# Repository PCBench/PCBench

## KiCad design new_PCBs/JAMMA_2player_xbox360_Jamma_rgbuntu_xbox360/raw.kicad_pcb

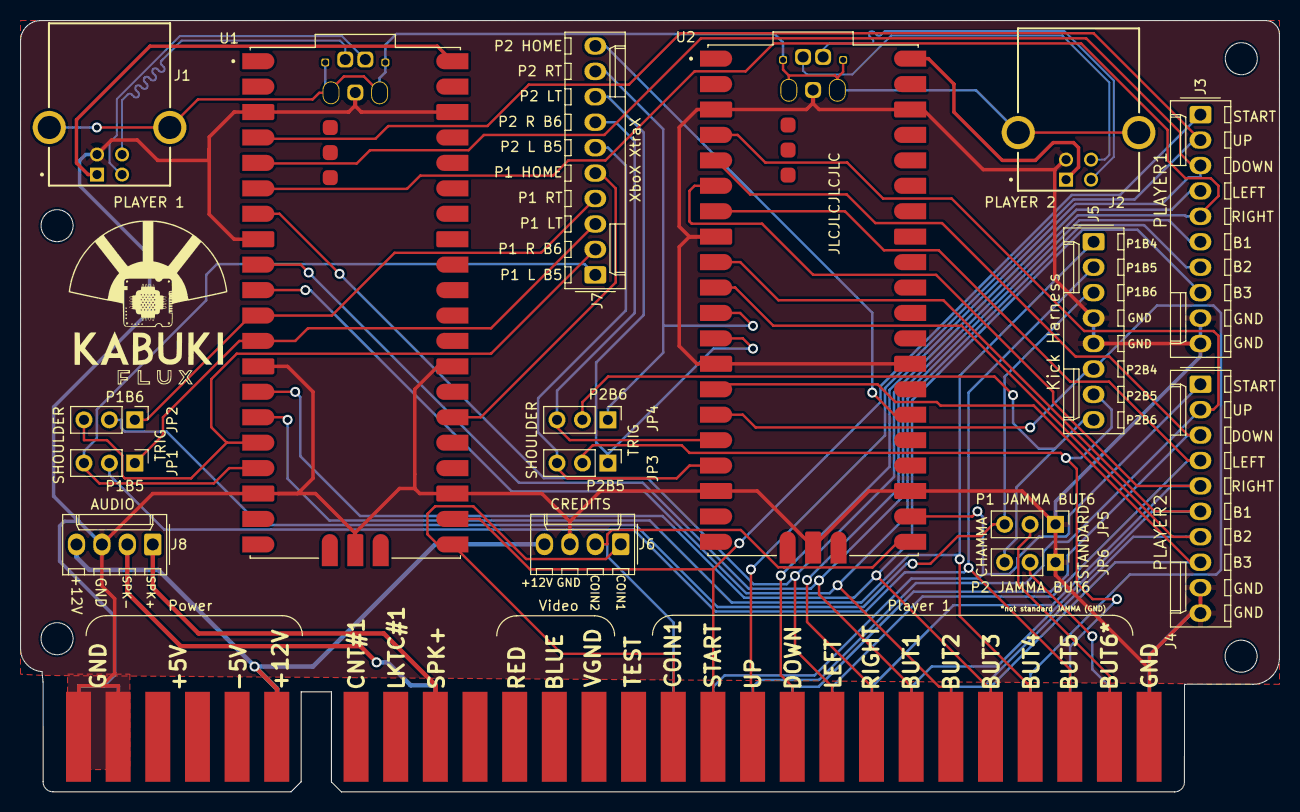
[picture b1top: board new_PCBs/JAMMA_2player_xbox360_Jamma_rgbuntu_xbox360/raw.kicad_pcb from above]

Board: 2 copper layers, 125.7 x 77.0 mm, 22 parts (0 on the bottom side), 47 nets.

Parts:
G1: LOGO; LogoKabuki_18mm
HOLE1, HOLE2, HOLE3, HOLE4: MountingHole_3.2mm_M3
J1: USB-B PICO1; USB-B
J2: USB-B PICO2; USB-B
J3: PLAYER1; Molex_KK-254_AE-6410-10A_1x10_P2.54mm_Vertical
J4: PLAYER2; Molex_KK-254_AE-6410-10A_1x10_P2.54mm_Vertical
J5: Kick Harness; Molex_KK-254_AE-6410-08A_1x08_P2.54mm_Vertical
J6: CREDITS; Molex_KK-254_AE-6410-04A_1x04_P2.54mm_Vertical
J7: XboX XtraX; Molex_KK-254_AE-6410-10A_1x10_P2.54mm_Vertical
J8: AUDIO; Molex_KK-254_AE-6410-04A_1x04_P2.54mm_Vertical
J9: JAMMA_edge_conn; JAMMA_edge
JP1: P1_B5_SELECTOR; PinHeader_1x03_P2.54mm_Vertical
JP2: P1_B6_SELECTOR; PinHeader_1x03_P2.54mm_Vertical
JP3: P2_B5_SELECTOR; PinHeader_1x03_P2.54mm_Vertical
JP4: P2_B6_SELECTOR; PinHeader_1x03_P2.54mm_Vertical
JP5: P1 JAMMA BUT6; PinHeader_1x03_P2.54mm_Vertical
JP6: P2 JAMMA BUT6; PinHeader_1x03_P2.54mm_Vertical
U1, U2: pi_pico; pi-pico

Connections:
/+12V: J6.4, J8.4, J9.6 (+12V), J9.F (+12V)
/GND: J1.4 (GND), J2.4 (GND), J3.9, J3.10, J4.9, J4.10, J5.4, J5.5, J6.3, J8.3, J9.1 (GND), J9.2 (GND), J9.28 (GND), J9.A (GND), J9.B (GND), J9.f (GND), JP5.1 (A), JP6.1 (A), U1.3 (GND), U1.8 (GND), U1.13 (GND), U1.18 (GND), U1.23 (GND), U1.28 (GND), U1.38 (GND), U1.D2 (GND), U1.TP1 (TP1_GND), U2.3 (GND), U2.8 (GND), U2.13 (GND), U2.18 (GND), U2.23 (GND), U2.28 (GND), U2.38 (GND), U2.D2 (GND), U2.TP1 (TP1_GND)
/P1_A_B1: J3.6, J9.22 (Player_1_Button_1), U1.9 (GP6)
/P1_B5: J5.2, J9.26 (Unused), JP1.2 (C)
/P1_B6: J5.3, JP2.2 (C), JP5.3 (B)
/P1_B_B2: J3.7, J9.23 (Player_1_Button_2), U1.10 (GP7)
/P1_COIN_B7: J6.1, J9.16 (Coin_1), U1.21 (GP16)
/P1_DPAD_DOWN: J3.3, J9.19 (Player_1_Down), U1.5 (GP3)
/P1_DPAD_LEFT: J3.4, J9.20 (Player_1_Left), U1.7 (GP5)
/P1_DPAD_RIGHT: J3.5, J9.21 (Player_1_Right), U1.6 (GP4)
/P1_DPAD_UP: J3.2, J9.18 (Player_1_Up), U1.4 (GP2)
/P1_HOME: J7.5, U1.26 (GP20)
/P1_JAMMA_B6_GND: J9.27 (GND), JP5.2 (C)
/P1_LT: J7.3, JP1.1 (A), U1.12 (GP9)
/P1_L_B5: J7.1, JP1.3 (B), U1.17 (GP13)
/P1_RT: J7.4, JP2.1 (A), U1.11 (GP8)
/P1_R_B6: J7.2, JP2.3 (B), U1.16 (GP12)
/P1_START_B8: J3.1, J9.17 (Player_1_Start), U1.22 (GP17)
/P1_X_B3: J3.8, J9.24 (Player_1_Button_3), U1.14 (GP10)
/P1_Y_B4: J5.1, J9.25 (Player_1_Button_4), U1.15 (GP11)
/P2_A_B1: J4.6, J9.Z (Player_2_Button_1), U2.9 (GP6)
/P2_B5: J5.7, J9.d (Unused), JP3.2 (C)
/P2_B6: J5.8, JP4.2 (C), JP6.3 (B)
/P2_B_B2: J4.7, J9.a (Player_2_Button_2), U2.10 (GP7)
/P2_COIN_B7: J6.2, J9.T (Coin_2), U2.21 (GP16)
/P2_DPAD_DOWN: J4.3, J9.W (Player_2_Down), U2.5 (GP3)
/P2_DPAD_LEFT: J4.4, J9.X (Player_2_Left), U2.7 (GP5)
/P2_DPAD_RIGHT: J4.5, J9.Y (Player_2_Right), U2.6 (GP4)
/P2_DPAD_UP: J4.2, J9.V (Player_2_Up), U2.4 (GP2)
/P2_HOME: J7.10, U2.26 (GP20)
/P2_JAMMA_B6_GND: J9.e (GND), JP6.2 (C)
/P2_LT: J7.8, JP3.1 (A), U2.12 (GP9)
/P2_L_B5: J7.6, JP3.3 (B), U2.17 (GP13)
/P2_RT: J7.9, JP4.1 (A), U2.11 (GP8)
/P2_R_B6: J7.7, JP4.3 (B), U2.16 (GP12)
/P2_START_B8: J4.1, J9.U (Player_2_Start), U2.22 (GP17)
/P2_X_B3: J4.8, J9.b (Player_2_Button_3), U2.14 (GP10)
/P2_Y_B4: J5.6, J9.c (Player_2_Button_4), U2.15 (GP11)
/PICO1_D+: J1.3 (D+), U1.TP3 (TP3_USB_DP)
/PICO1_D-: J1.2 (D-), U1.TP2 (TP2_USB_DM)
/PICO2_D+: J2.3 (D+), U2.TP3 (TP3_USB_DP)
/PICO2_D-: J2.2 (D-), U2.TP2 (TP2_USB_DM)
/SPK+: J8.1, J9.10 (Speaker+)
/SPK-: J8.2, J9.L (Speaker-)
/USB_PICO1_VCC: J1.1 (VCC), U1.40 (VBUS)
/USB_PICO2_VCC: J2.1 (VCC), U2.40 (VBUS)
/USB_SHIELD: J1.S1 (SHIELD), J1.S2 (SHIELD), J2.S1 (SHIELD), J2.S2 (SHIELD), U1.A (USB_SHIELD), U1.B (USB_SHIELD), U1.C (USB_SHIELD), U1.D (USB_SHIELD), U2.A (USB_SHIELD), U2.B (USB_SHIELD), U2.C (USB_SHIELD), U2.D (USB_SHIELD)

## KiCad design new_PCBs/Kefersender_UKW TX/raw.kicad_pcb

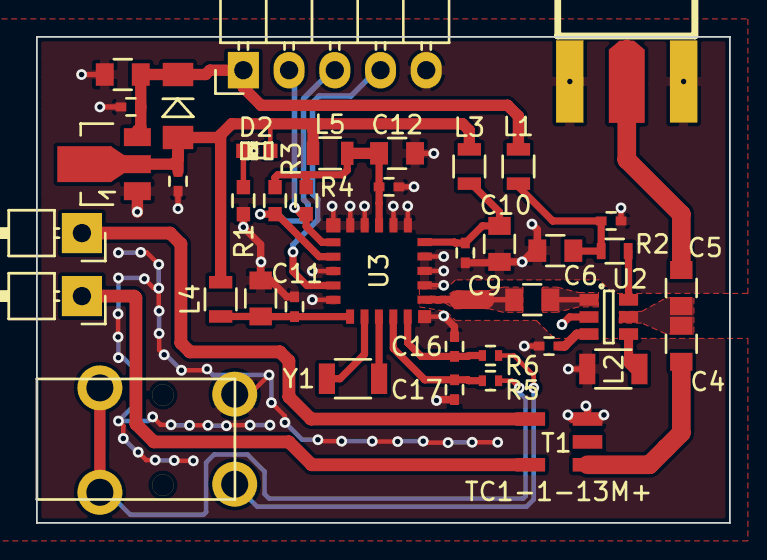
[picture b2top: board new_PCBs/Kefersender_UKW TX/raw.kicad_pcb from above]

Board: 2 copper layers, 38.5 x 27.0 mm, 40 parts (0 on the bottom side), 27 nets.

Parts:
C1, C3, C7, C8, C13, C14, C15: 100n; C_0402
C2, C6, C10, C11, C12: 22µ; C_0805
C4, C5, C9: 1nF; C_0805
C16, C17: 100p; C_0402
CON1: LUM1503
D1: 1n4148; Diode-MiniMELF_Standard
D2: grün; LED-0603
L1, L3, L4, L5: 10µH; R_0805
L2: 470nH; R_1206
P1, P2: CONN_01X01; Pin_Header_Angled_1x01
P3: CONN_01X05; Pin_Header_Angled_1x05
R1: 100; C_0603
R2: 220; R_0603
R3, R4: 4,7k; C_0603
R5, R6: 1k; R_0402
SMA_E1: Platinenkantenbuchse; SMA_EDGE
T1: TC1-1-13M+; AT224-1A
U1: AP1117D33; SOT89-3_Housing
U2: THS9001; SOT-23-6
U3: Alps_603A
Y1: 32,768kHz; R_1206

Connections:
+3V3: C3.1, D1.2, D2.2, L3.1, L4.1, L5.1, U1.2
+5V: C1.1, C2.1, D1.1, L1.2, P3.1, U1.3
/RDS: P3.4, U3.16
/SCL: P3.3, R3.2, U3.14
/SDA: P3.2, R4.2, U3.13
/Ton_L: CON1.2, R5.2
/Ton_R: CON1.3, R6.1
GND: C1.2, C2.2, C3.2, C6.2, C7.2, C8.2, C10.2, C11.2, C12.2, C13.2, C14.2, C15.2, C16.2, C17.2, CON1.1, L2.1, P3.5, R1.2, SMA_E1.0, SMA_E1.2, T1.1, U1.1, U2.2, U3.1, U3.3, U3.4, U3.5, U3.7, U3.8, U3.10, U3.11, U3.12, U3.15, U3.17
unnamed: C4.1, T1.4
unnamed: C4.2, C5.2, U2.5
unnamed: C5.1, SMA_E1.1
unnamed: C6.1, C7.1, L1.1, R2.1
unnamed: C8.1, U2.3
unnamed: C9.1, U2.1
unnamed: C9.2, U3.2
unnamed: C10.1, C13.1, L3.2, U3.6
unnamed: C11.1, C14.1, L4.2, U3.18
unnamed: C12.1, C15.1, L5.2, R3.1, R4.1, U3.9
unnamed: C16.1, R6.2, U3.22
unnamed: C17.1, R5.1, U3.21
unnamed: D2.1, R1.1
unnamed: L2.2, U2.4
unnamed: P1.1, T1.2
unnamed: P2.1, T1.3
unnamed: R2.2, U2.6
unnamed: U3.19, Y1.1
unnamed: U3.20, Y1.2

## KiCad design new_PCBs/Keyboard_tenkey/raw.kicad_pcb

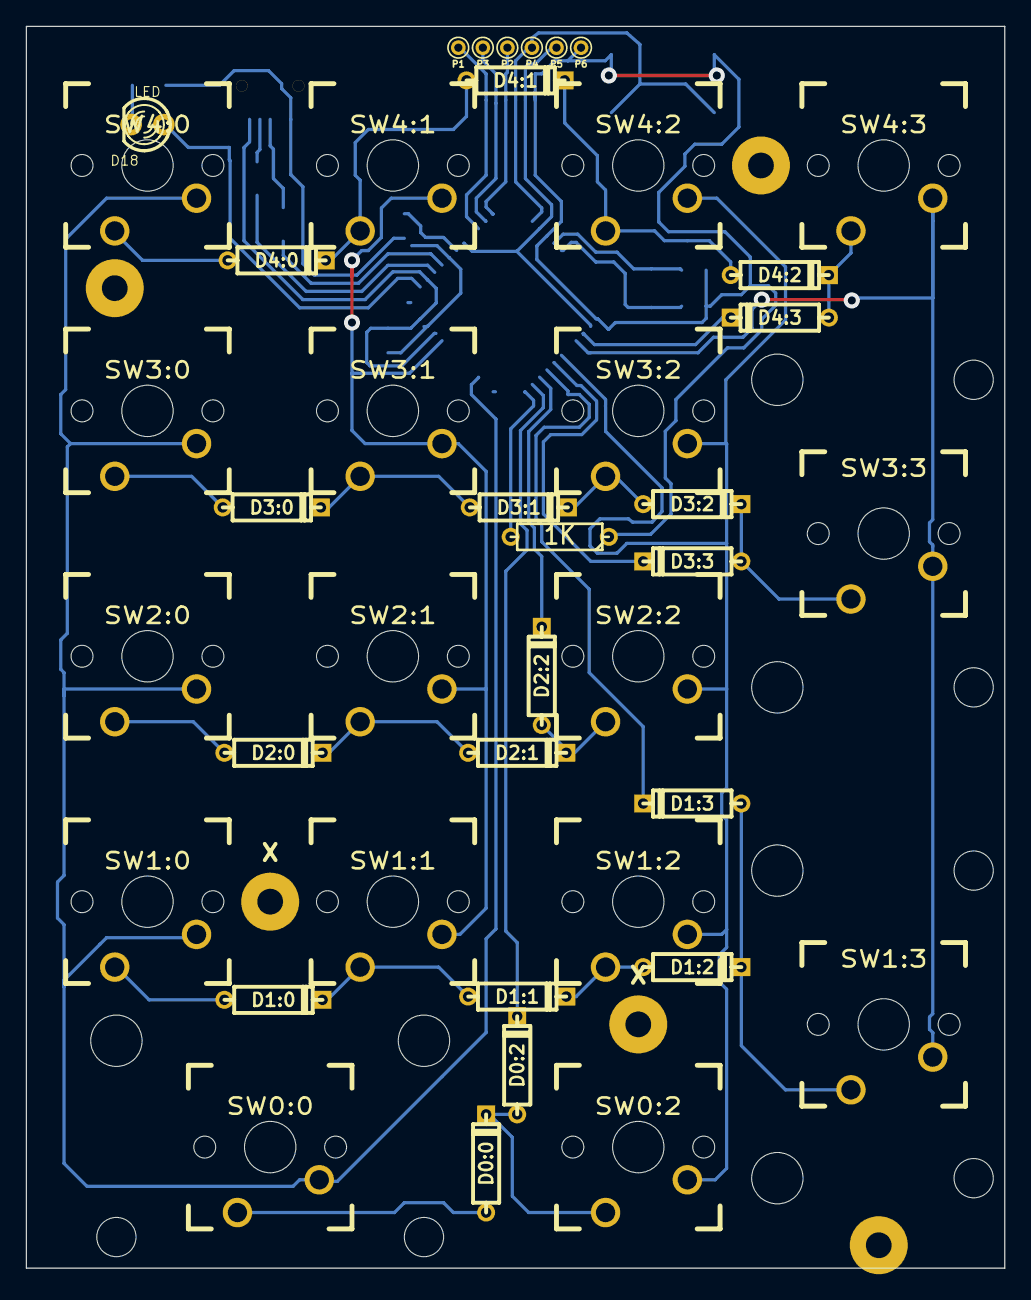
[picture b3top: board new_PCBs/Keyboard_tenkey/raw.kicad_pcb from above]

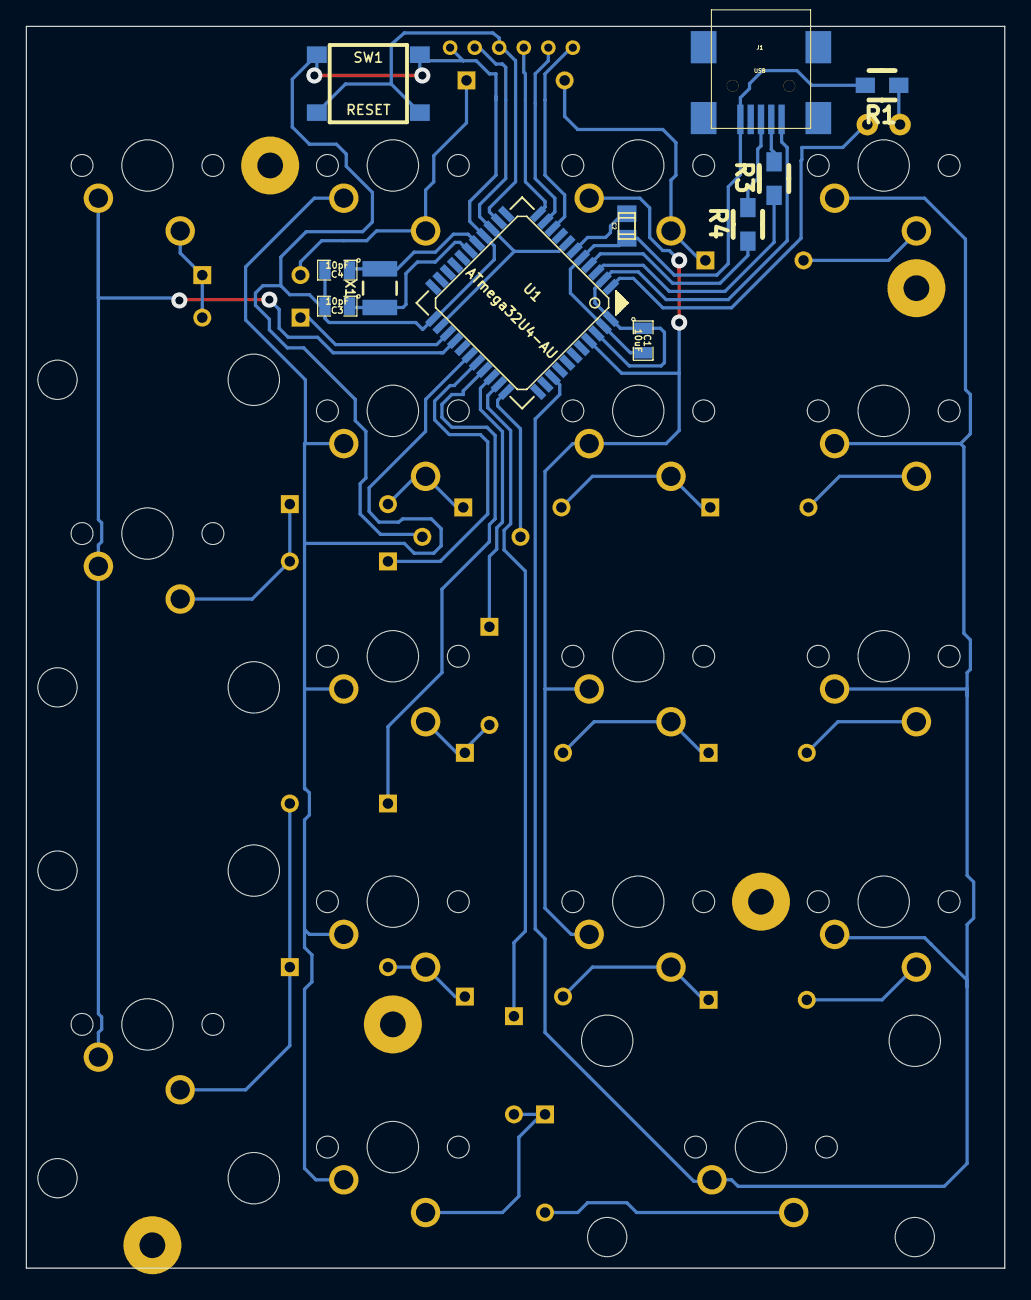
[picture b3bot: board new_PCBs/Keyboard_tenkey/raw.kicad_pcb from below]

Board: 2 copper layers, 75.9 x 96.4 mm, 55 parts (11 on the bottom side), 42 nets.

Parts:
C1: 10uF; SM0805
C2: 1uF; c_0805
C3, C4: 10pF; SM0805
D0:0, D0:2, D1:0, D1:1, D1:2, D1:3, D2:0, D2:1, D2:2, D3:0, D3:1, D3:2, D3:3, D4:0, D4:1, D4:2, D4:3: DIODE; D3
D18: LED; LED-3MM
J1: USB; USB-MINI-B-SMD
P1: SCK; PINTST
P2: MISO; PINTST
P3: MOSI; PINTST
P4: RESET; PINTST
P5: 5V; PINTST
P6: GND; PINTST
R1: 220; Resistor_SMD0805_HandSoldering
R3, R4: 22; Resistor_SMD0805_HandSoldering
R5: 1K; R3
SW0:0: NUM_0; CHERRY_PCB_200H
SW0:2: DOT; CHERRY_PCB_100H
SW1: RESET; SW_PUSH_SMD
SW1:0: NUM_1; CHERRY_PCB_100H
SW1:1: NUM_2; CHERRY_PCB_100H
SW1:2: NUM_3; CHERRY_PCB_100H
SW1:3: ENTER; CHERRY_PCB_200V
SW2:0: NUM_4; CHERRY_PCB_100H
SW2:1: NUM_5; CHERRY_PCB_100H
SW2:2: NUM_6; CHERRY_PCB_100H
SW3:0: NUM_7; CHERRY_PCB_100H
SW3:1: NUM_8; CHERRY_PCB_100H
SW3:2: NUM_9; CHERRY_PCB_100H
SW3:3: PLUS; CHERRY_PCB_200V
SW4:0: NUM_LCK; CHERRY_PCB_100H
SW4:1: DIVIDE; CHERRY_PCB_100H
SW4:2: MULTIPLY; CHERRY_PCB_100H
SW4:3: MINUS; CHERRY_PCB_100H
U1: ATmega32U4-AU; lqfp44
X: SolderWirePad_single_2mmDrill
X1: 16 MHz; SMD-3225
X#2: SolderWirePad_single_2mmDrill

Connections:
/+5V: C1.1, J1.1, P5.1, U1.2, U1.7, U1.14, U1.24, U1.34, U1.42, U1.44
/COL0: SW0:0.2, SW1:0.2, SW2:0.2, SW3:0.2, SW4:0.2, U1.36
/COL1: SW1:1.2, SW2:1.2, SW3:1.2, SW4:1.2, U1.41
/COL2: SW0:2.2, SW1:2.2, SW2:2.2, SW3:2.2, SW4:2.2, U1.28
/COL3: SW1:3.2, SW3:3.2, SW4:3.2, U1.26
/LED_A: D18.1, U1.1
/MISO: P2.1, U1.11
/MOSI: P3.1, U1.10
/RESET: P4.1, SW1.2, U1.13
/ROW0: D0:2.2, U1.32
/ROW1: D1:3.2, U1.30
/ROW2: D2:2.2, U1.31
/ROW3: D3:3.2, U1.29
/ROW4: D4:3.2, U1.25
/SCK: P1.1, U1.9
GND: C1.2, C2.2, C3.2, C4.2, J1.5, P6.1, R1.2, R5.1, SW1.1, U1.5, U1.15, U1.23, U1.35, U1.43
unnamed: C2.1, U1.6
unnamed: C3.1, U1.17, X1.1
unnamed: C4.1, U1.16, X1.2
unnamed: D0:0.1, SW0:0.1
unnamed: D0:0.2, D0:2.1, SW0:2.1
unnamed: D1:0.1, SW1:0.1
unnamed: D1:0.2, D1:1.1, SW1:1.1
unnamed: D1:1.2, D1:2.1, SW1:2.1
unnamed: D1:2.2, D1:3.1, SW1:3.1
unnamed: D2:0.1, SW2:0.1
unnamed: D2:0.2, D2:1.1, SW2:1.1
unnamed: D2:1.2, D2:2.1, SW2:2.1
unnamed: D3:0.1, SW3:0.1
unnamed: D3:0.2, D3:1.1, SW3:1.1
unnamed: D3:1.2, D3:2.1, SW3:2.1
unnamed: D3:2.2, D3:3.1, SW3:3.1
unnamed: D4:0.1, SW4:0.1
unnamed: D4:0.2, D4:1.1, SW4:1.1
unnamed: D4:1.2, D4:2.1, SW4:2.1
unnamed: D4:2.2, D4:3.1, SW4:3.1
unnamed: D18.2, R1.1
unnamed: J1.2, R3.2
unnamed: J1.3, R4.2
unnamed: R3.1, U1.3
unnamed: R4.1, U1.4
unnamed: R5.2, U1.33

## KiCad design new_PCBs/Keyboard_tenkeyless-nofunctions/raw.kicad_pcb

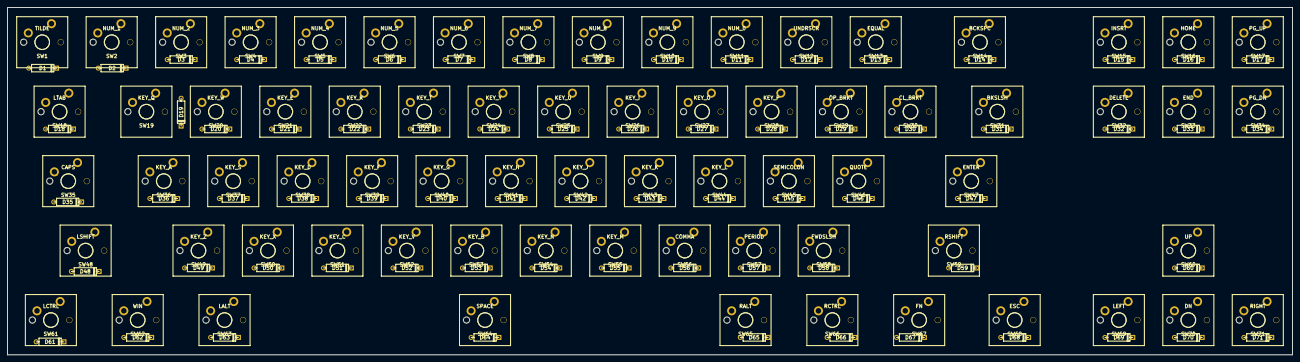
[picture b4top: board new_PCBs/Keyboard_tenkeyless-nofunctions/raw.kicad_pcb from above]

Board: 2 copper layers, 352.4 x 95.2 mm, 142 parts (0 on the bottom side), 93 nets.

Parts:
D1, D2, D3, D4, D5, D6, D7, D8, D9, D10, D11, D12, D13, D14, D15, D16, D17, D18, D19, D20, D21, D22, D23, D24, D25, D26, D27, D28, D29, D30, D31, D32, D33, D34, D35, D36, D37, D38, D39, D40, D41, D42, D43, D44, D45, D46, D47, D48, D49, D50, D51, D52, D53, D54, D55, D56, D57, D58, D59, D60, D61, D62, D63, D64, D65, D66, D67, D68, D69, D70, D71: DIODE; D3
SW1: TILDE; KEYMODULE_MX_PINS
SW2: NUM_1; KEYMODULE_MX_PINS
SW3: NUM_2; KEYMODULE_MX_PINS
SW4: NUM_3; KEYMODULE_MX_PINS
SW5: NUM_4; KEYMODULE_MX_PINS
SW6: NUM_5; KEYMODULE_MX_PINS
SW7: NUM_6; KEYMODULE_MX_PINS
SW8: NUM_7; KEYMODULE_MX_PINS
SW9: NUM_8; KEYMODULE_MX_PINS
SW10: NUM_9; KEYMODULE_MX_PINS
SW11: NUM_0; KEYMODULE_MX_PINS
SW12: UNDRSCR; KEYMODULE_MX_PINS
SW13: EQUAL; KEYMODULE_MX_PINS
SW14: BCKSPC; KEYMODULE_MX_PINS
SW15: INSRT; KEYMODULE_MX_PINS
SW16: HOME; KEYMODULE_MX_PINS
SW17: PG_UP; KEYMODULE_MX_PINS
SW18: LTAB; KEYMODULE_MX_PINS
SW19: KEY_Q; KEYMODULE_MX_PINS
SW20: KEY_W; KEYMODULE_MX_PINS
SW21: KEY_E; KEYMODULE_MX_PINS
SW22: KEY_R; KEYMODULE_MX_PINS
SW23: KEY_T; KEYMODULE_MX_PINS
SW24: KEY_Y; KEYMODULE_MX_PINS
SW25: KEY_U; KEYMODULE_MX_PINS
SW26: KEY_I; KEYMODULE_MX_PINS
SW27: KEY_O; KEYMODULE_MX_PINS
SW28: KEY_P; KEYMODULE_MX_PINS
SW29: OP_BRKT; KEYMODULE_MX_PINS
SW30: CL_BRKT; KEYMODULE_MX_PINS
SW31: BKSLSH; KEYMODULE_MX_PINS
SW32: DELETE; KEYMODULE_MX_PINS
SW33: END; KEYMODULE_MX_PINS
SW34: PG_DN; KEYMODULE_MX_PINS
SW35: CAPS; KEYMODULE_MX_PINS
SW36: KEY_A; KEYMODULE_MX_PINS
SW37: KEY_S; KEYMODULE_MX_PINS
SW38: KEY_D; KEYMODULE_MX_PINS
SW39: KEY_F; KEYMODULE_MX_PINS
SW40: KEY_G; KEYMODULE_MX_PINS
SW41: KEY_H; KEYMODULE_MX_PINS
SW42: KEY_J; KEYMODULE_MX_PINS
SW43: KEY_K; KEYMODULE_MX_PINS
SW44: KEY_L; KEYMODULE_MX_PINS
SW45: SEMICOLON; KEYMODULE_MX_PINS
SW46: QUOTE; KEYMODULE_MX_PINS
SW47: ENTER; KEYMODULE_MX_PINS
SW48: LSHIFT; KEYMODULE_MX_PINS
SW49: KEY_Z; KEYMODULE_MX_PINS
SW50: KEY_X; KEYMODULE_MX_PINS
SW51: KEY_C; KEYMODULE_MX_PINS
SW52: KEY_V; KEYMODULE_MX_PINS
SW53: KEY_B; KEYMODULE_MX_PINS
SW54: KEY_N; KEYMODULE_MX_PINS
SW55: KEY_M; KEYMODULE_MX_PINS
SW56: COMMA; KEYMODULE_MX_PINS
SW57: PERIOD; KEYMODULE_MX_PINS
SW58: FWDSLSH; KEYMODULE_MX_PINS
SW59: RSHIFT; KEYMODULE_MX_PINS
SW60: UP; KEYMODULE_MX_PINS
SW61: LCTRL; KEYMODULE_MX_PINS
SW62: WIN; KEYMODULE_MX_PINS
SW63: LALT; KEYMODULE_MX_PINS
SW64: SPACE; KEYMODULE_MX_PINS
SW65: RALT; KEYMODULE_MX_PINS
SW66: RCTRL; KEYMODULE_MX_PINS
SW67: FN; KEYMODULE_MX_PINS
SW68: ESC; KEYMODULE_MX_PINS
SW69: LEFT; KEYMODULE_MX_PINS
SW70: DN; KEYMODULE_MX_PINS
SW71: RIGHT; KEYMODULE_MX_PINS

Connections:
/COL0: D1.2, D18.2, D35.2, D48.2, D61.2
/COL1: D2.2, D19.2, D36.2, D62.2
/COL2: D3.2, D20.2, D37.2, D49.2, D63.2
/COL3: D4.2, D21.2, D38.2, D50.2
/COL4: D5.2, D22.2, D39.2, D51.2
/COL5: D6.2, D23.2, D40.2, D52.2
/COL6: D7.2, D24.2, D41.2, D53.2, D64.2
/COL7: D8.2, D25.2, D42.2, D54.2
/COL9: D9.2, D26.2, D43.2, D55.2
/COL10: D10.2, D27.2, D44.2, D56.2
/COL11: D11.2, D28.2, D45.2, D57.2, D65.2
/COL12: D12.2, D29.2, D46.2, D58.2, D66.2
/COL13: D13.2, D30.2, D47.2, D67.2
/COL14: D14.2, D31.2, D59.2, D68.2
/COL15: D15.2, D32.2, D69.2
/COL16: D16.2, D33.2, D60.2, D70.2
/COL17: D17.2, D34.2, D71.2
/ROW0: SW61.1, SW62.1, SW63.1, SW64.1, SW65.1, SW66.1, SW67.1, SW68.1, SW69.1, SW70.1, SW71.1
/ROW1: SW48.1, SW49.1, SW50.1, SW51.1, SW52.1, SW53.1, SW54.1, SW55.1, SW56.1, SW57.1, SW58.1, SW59.1, SW60.1
/ROW2: SW35.1, SW36.1, SW37.1, SW38.1, SW39.1, SW40.1, SW41.1, SW42.1, SW43.1, SW44.1, SW45.1, SW46.1, SW47.1
/ROW3: SW18.1, SW19.1, SW20.1, SW21.1, SW22.1, SW23.1, SW24.1, SW25.1, SW26.1, SW27.1, SW28.1, SW29.1, SW30.1, SW31.1, SW32.1, SW33.1, SW34.1
/ROW4: SW1.1, SW2.1, SW3.1, SW4.1, SW5.1, SW6.1, SW7.1, SW8.1, SW9.1, SW10.1, SW11.1, SW12.1, SW13.1, SW14.1, SW15.1, SW16.1, SW17.1
unnamed: D1.1, SW1.2
unnamed: D2.1, SW2.2
unnamed: D3.1, SW3.2
unnamed: D4.1, SW4.2
unnamed: D5.1, SW5.2
unnamed: D6.1, SW6.2
unnamed: D7.1, SW7.2
unnamed: D8.1, SW8.2
unnamed: D9.1, SW9.2
unnamed: D10.1, SW10.2
unnamed: D11.1, SW11.2
unnamed: D12.1, SW12.2
unnamed: D13.1, SW13.2
unnamed: D14.1, SW14.2
unnamed: D15.1, SW15.2
unnamed: D16.1, SW16.2
unnamed: D17.1, SW17.2
unnamed: D18.1, SW18.2
unnamed: D19.1, SW19.2
unnamed: D20.1, SW20.2
unnamed: D21.1, SW21.2
unnamed: D22.1, SW22.2
unnamed: D23.1, SW23.2
unnamed: D24.1, SW24.2
unnamed: D25.1, SW25.2
unnamed: D26.1, SW26.2
unnamed: D27.1, SW27.2
unnamed: D28.1, SW28.2
unnamed: D29.1, SW29.2
unnamed: D30.1, SW30.2
unnamed: D31.1, SW31.2
unnamed: D32.1, SW32.2
unnamed: D33.1, SW33.2
unnamed: D34.1, SW34.2
unnamed: D35.1, SW35.2
unnamed: D36.1, SW36.2
unnamed: D37.1, SW37.2
unnamed: D38.1, SW38.2
unnamed: D39.1, SW39.2
unnamed: D40.1, SW40.2
unnamed: D41.1, SW41.2
unnamed: D42.1, SW42.2
unnamed: D43.1, SW43.2
unnamed: D44.1, SW44.2
unnamed: D45.1, SW45.2
unnamed: D46.1, SW46.2
unnamed: D47.1, SW47.2
unnamed: D48.1, SW48.2
unnamed: D49.1, SW49.2
unnamed: D50.1, SW50.2
unnamed: D51.1, SW51.2
unnamed: D52.1, SW52.2
unnamed: D53.1, SW53.2
unnamed: D54.1, SW54.2
unnamed: D55.1, SW55.2
unnamed: D56.1, SW56.2
unnamed: D57.1, SW57.2
unnamed: D58.1, SW58.2
unnamed: D59.1, SW59.2
unnamed: D60.1, SW60.2
unnamed: D61.1, SW61.2
unnamed: D62.1, SW62.2
unnamed: D63.1, SW63.2
unnamed: D64.1, SW64.2
unnamed: D65.1, SW65.2
unnamed: D66.1, SW66.2
unnamed: D67.1, SW67.2
unnamed: D68.1, SW68.2
unnamed: D69.1, SW69.2
unnamed: D70.1, SW70.2
unnamed: D71.1, SW71.2

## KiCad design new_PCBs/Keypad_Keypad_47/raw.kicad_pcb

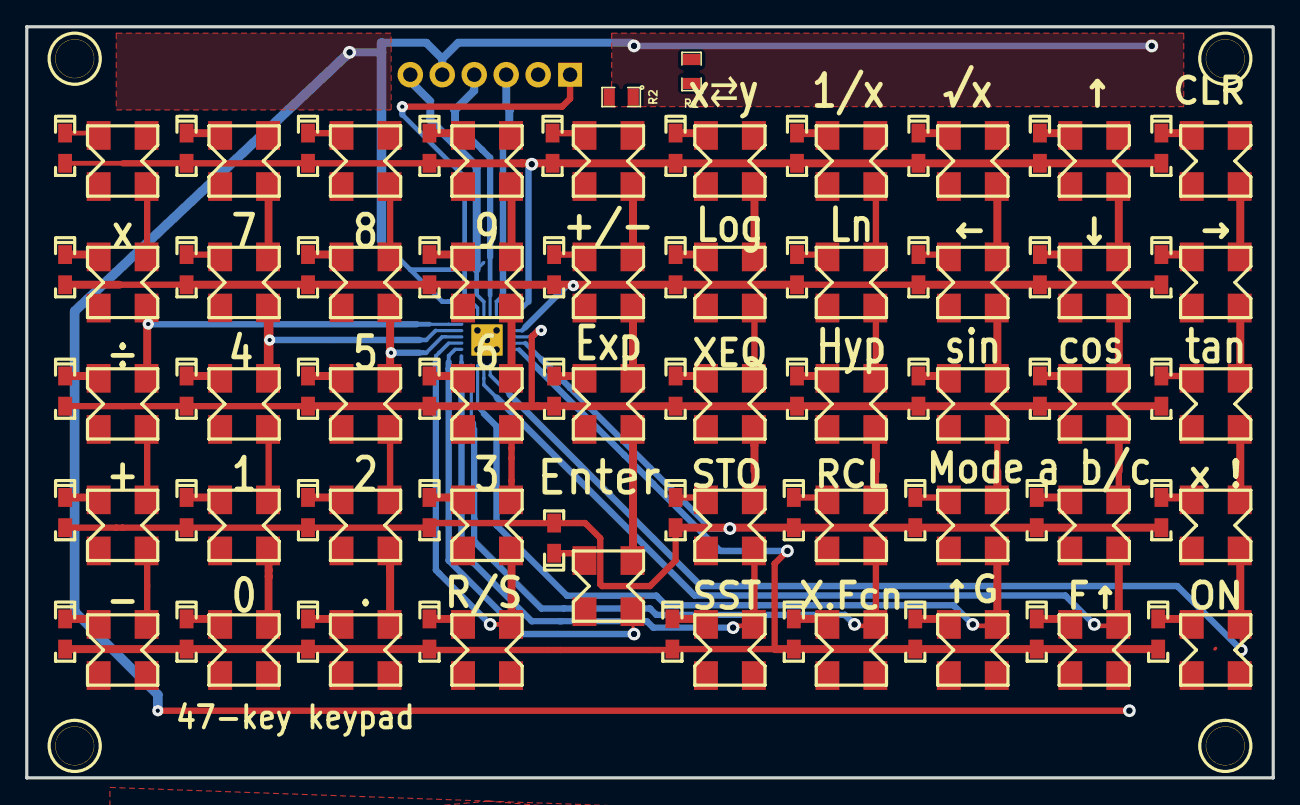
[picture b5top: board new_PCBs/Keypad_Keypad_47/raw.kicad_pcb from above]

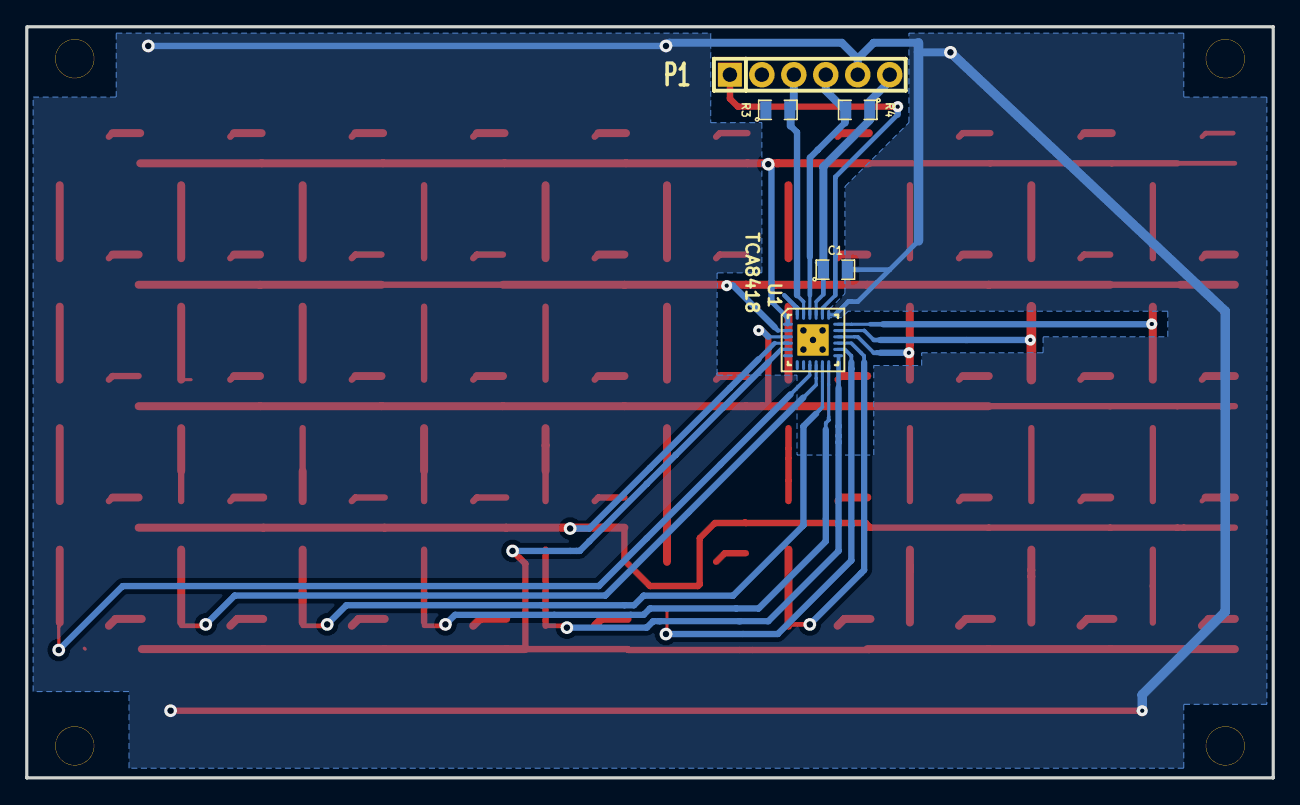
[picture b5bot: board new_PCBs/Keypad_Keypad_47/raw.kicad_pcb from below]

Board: 2 copper layers, 99.1 x 59.7 mm, 109 parts (5 on the bottom side), 70 nets.

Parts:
1PIN, 1PIN#2, 1PIN#3, 1PIN#4: P***; 1_Pin
C1: 1u; SM0805
D1, D2, D3, D4, D5, D6, D7, D8, D9, D10, D11, D12, D13, D14, D15, D16, D17, D18, D19, D20, D21, D22, D23, D24, D25, D26, D27, D28, D29, D30, D31, D32, D33, D34, D35, D36, D37, D38, D39, D40, D41, D42, D43, D44, D45, D46, D47, D48, D49: 1n914; SOD_323
P1: KBD_6; SIL-6
R1, R2: 10K; SM0805
R3, R4: 4K7; SM0805
SW1, SW2, SW3, SW4, SW5, SW6, SW7, SW8, SW9, SW10, SW11, SW12, SW13, SW14, SW15, SW16, SW17, SW18, SW19, SW20, SW21, SW22, SW23, SW24, SW25, SW26, SW27, SW28, SW29, SW30, SW31, SW32, SW33, SW34, SW35, SW36, SW37, SW38, SW39, SW40, SW41, SW42, SW43, SW44, SW45, SW46, SW47, SW48, SW49: MX; TACTILE_EVQPQ_5MM
U1: TCA8418; QFN24

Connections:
//INT: P1.2, R2.2, U1.24
//RESET: P1.1, R1.2, U1.20
/Col0: SW1.2, SW2.2, SW3.2, SW4.2, SW5.2, U1.18
/Col1: SW6.2, SW7.2, SW8.2, SW9.2, SW10.2, U1.17
/Col2: SW11.2, SW12.2, SW13.2, SW14.2, SW15.2, U1.16
/Col3: SW16.2, SW17.2, SW18.2, SW19.2, SW20.2, U1.15
/Col4: SW21.2, SW22.2, SW23.2, SW24.2, U1.14
/Col5: SW25.2, SW26.2, SW27.2, SW28.2, SW29.2, U1.13
/Col6: SW30.2, SW31.2, SW32.2, SW33.2, SW34.2, U1.12
/Col7: SW35.2, SW36.2, SW37.2, SW38.2, SW39.2, U1.11
/Col8: SW40.2, SW41.2, SW42.2, SW43.2, SW44.2, U1.10
/Col9: SW45.2, SW46.2, SW47.2, SW48.2, SW49.2, U1.9
/Row0: D5.1, D10.1, D15.1, D20.1, D29.1, D34.1, D39.1, D44.1, D49.1, U1.5
/Row1: D4.1, D9.1, D14.1, D19.1, D24.1, D28.1, D33.1, D38.1, D43.1, D48.1, U1.4
/Row2: D3.1, D8.1, D13.1, D18.1, D23.1, D27.1, D32.1, D37.1, D42.1, D47.1, U1.3
/Row3: D2.1, D7.1, D12.1, D17.1, D22.1, D26.1, D31.1, D36.1, D41.1, D46.1, U1.2
/Row4: D1.1, D6.1, D11.1, D16.1, D21.1, D25.1, D30.1, D35.1, D40.1, D45.1, U1.1
/SCL: P1.3, R3.2, U1.23
/SDA: P1.4, R4.2, U1.22
GND: C1.2, P1.5, U1.19
unnamed: D1.2, SW1.1
unnamed: D2.2, SW2.1
unnamed: D3.2, SW3.1
unnamed: D4.2, SW4.1
unnamed: D5.2, SW5.1
unnamed: D6.2, SW6.1
unnamed: D7.2, SW7.1
unnamed: D8.2, SW8.1
unnamed: D9.2, SW9.1
unnamed: D10.2, SW10.1
unnamed: D11.2, SW11.1
unnamed: D12.2, SW12.1
unnamed: D13.2, SW13.1
unnamed: D14.2, SW14.1
unnamed: D15.2, SW15.1
unnamed: D16.2, SW16.1
unnamed: D17.2, SW17.1
unnamed: D18.2, SW18.1
unnamed: D19.2, SW19.1
unnamed: D20.2, SW20.1
unnamed: D21.2, SW21.1
unnamed: D22.2, SW22.1
unnamed: D23.2, SW23.1
unnamed: D24.2, SW24.1
unnamed: D25.2, SW25.1
unnamed: D26.2, SW26.1
unnamed: D27.2, SW27.1
unnamed: D28.2, SW28.1
unnamed: D29.2, SW29.1
unnamed: D30.2, SW30.1
unnamed: D31.2, SW31.1
unnamed: D32.2, SW32.1
unnamed: D33.2, SW33.1
unnamed: D34.2, SW34.1
unnamed: D35.2, SW35.1
unnamed: D36.2, SW36.1
unnamed: D37.2, SW37.1
unnamed: D38.2, SW38.1
unnamed: D39.2, SW39.1
unnamed: D40.2, SW40.1
unnamed: D41.2, SW41.1
unnamed: D42.2, SW42.1
unnamed: D43.2, SW43.1
unnamed: D44.2, SW44.1
unnamed: D45.2, SW45.1
unnamed: D46.2, SW46.1
unnamed: D47.2, SW47.1
unnamed: D48.2, SW48.1
unnamed: D49.2, SW49.1
VCC: C1.1, P1.6, R1.1, R2.1, R3.1, R4.1, U1.21

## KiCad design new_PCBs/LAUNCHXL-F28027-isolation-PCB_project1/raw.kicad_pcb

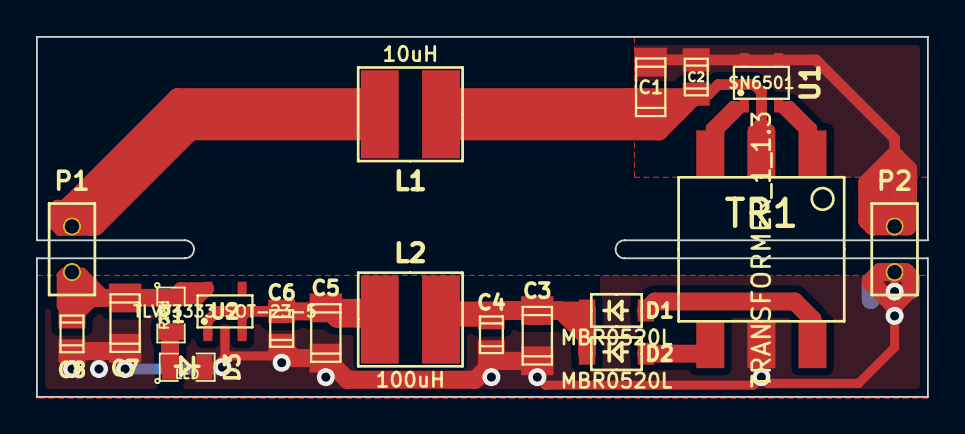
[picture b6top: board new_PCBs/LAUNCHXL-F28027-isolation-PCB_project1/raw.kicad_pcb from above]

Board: 2 copper layers, 49.5 x 20.0 mm, 19 parts (0 on the bottom side), 12 nets.

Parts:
C1, C3, C5, C7: 4.7u; c_1206
C2, C4, C6, C8: 100n; c_0805
D1, D2: MBR0520L; SOD-123
D3: LED; SM0805
L1: 10uH; VLCF5020
L2: 100uH; VLCF5020
P1, P2: CONN_2; PIN_ARRAY_2X1
R1: Rled; SM0805
TR1: TRANSFORMER_1_1.3; transf_isol_wurth
U1: SN6501; SOT23-5
U2: TLV73333 SOT-23-5; SOT23-5

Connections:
3.3V: L1.1, P1.2
3.3V isol: C7.1, C8.1, P1.1, R1.1, U2.5
GND: C1.2, C2.2, P2.2, U1.4, U1.5
GND_isol: C3.2, C4.2, C5.2, C6.2, C7.2, C8.2, D3.2, P2.1, TR1.5, U2.2
unnamed: C1.1, C2.1, L1.2, TR1.2, U1.2
unnamed: D3.1, R1.2
unnamed: TR1.1, U1.3
unnamed: TR1.3, U1.1
unnamed: C3.1, C4.1, D1.2, D2.2, L2.1
unnamed: D1.1, TR1.6
unnamed: D2.1, TR1.4
unnamed: C5.1, C6.1, L2.2, U2.1, U2.3

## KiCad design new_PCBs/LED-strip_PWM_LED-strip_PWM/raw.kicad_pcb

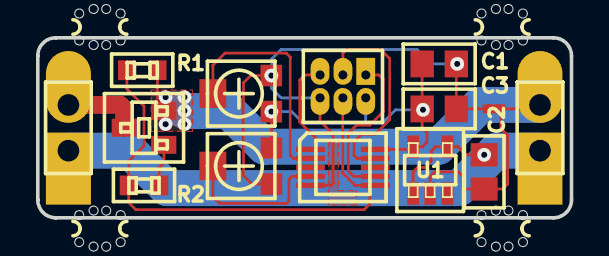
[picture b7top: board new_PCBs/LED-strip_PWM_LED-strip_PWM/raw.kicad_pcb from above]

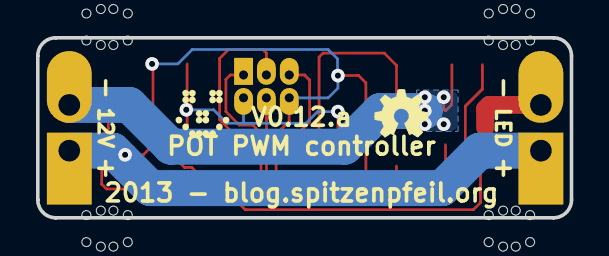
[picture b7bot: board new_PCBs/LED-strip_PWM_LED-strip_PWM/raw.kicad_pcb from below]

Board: 2 copper layers, 29.7 x 10.0 mm, 20 parts (2 on the bottom side), 12 nets.

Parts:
C1, C2: 100nF; MADW__C0805
C3: 4.7µF; MADW__C0805
G1: OSHW-logo_silkscreen_3mm
G2: LED_smile_silkscreen_3mm
IC1: MADW__ATTINY13-MM; MADW__MLF10
JP1: ISP; MADW__PIN_ARRAY_3x2_1.27mm
NJ1: NET-JOIN; MADW__SMD-net-noin-0.5mm
P1, P2: CONN_2; MADW__SIL-2
R1: 100k; MADW__R0603_2
R2: 150R; MADW__R0603_2
RV1, RV2: 50k; MADW__TC33X-POT
T1: AO3400; MADW__SOT23
U1: MCP1804-SOT23-5; MADW__SOT23-5
mouse-bite-1mm, mouse-bite-1mm#2, mouse-bite-1mm#3, mouse-bite-1mm#4: VAL**; MADW__mouse-bite-1mm-slot

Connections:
/MISO: IC1.7, JP1.1
/MOSI: IC1.6, JP1.4, R1.2, R2.1
/POT1: IC1.2, RV1.2
/POT2: IC1.4, RV2.2
/RESET: IC1.1, JP1.5
/SCK: IC1.9, JP1.3
/Vin: C2.1, P1.1, P2.1, U1.1, U1.4
/drain: P2.2, T1.3
GND: C1.2, C3.2, IC1.5, JP1.6, NJ1.1, RV1.3, RV2.1
GNDPWR: C2.2, NJ1.2, P1.2, R1.1, T1.2, U1.2
unnamed: R2.2, T1.1
VCC: C1.1, C3.1, IC1.10, JP1.2, RV1.1, RV2.3, U1.5
